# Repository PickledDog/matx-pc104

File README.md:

# matx-pc104
 microATX carrier board for PC/104 SBCs

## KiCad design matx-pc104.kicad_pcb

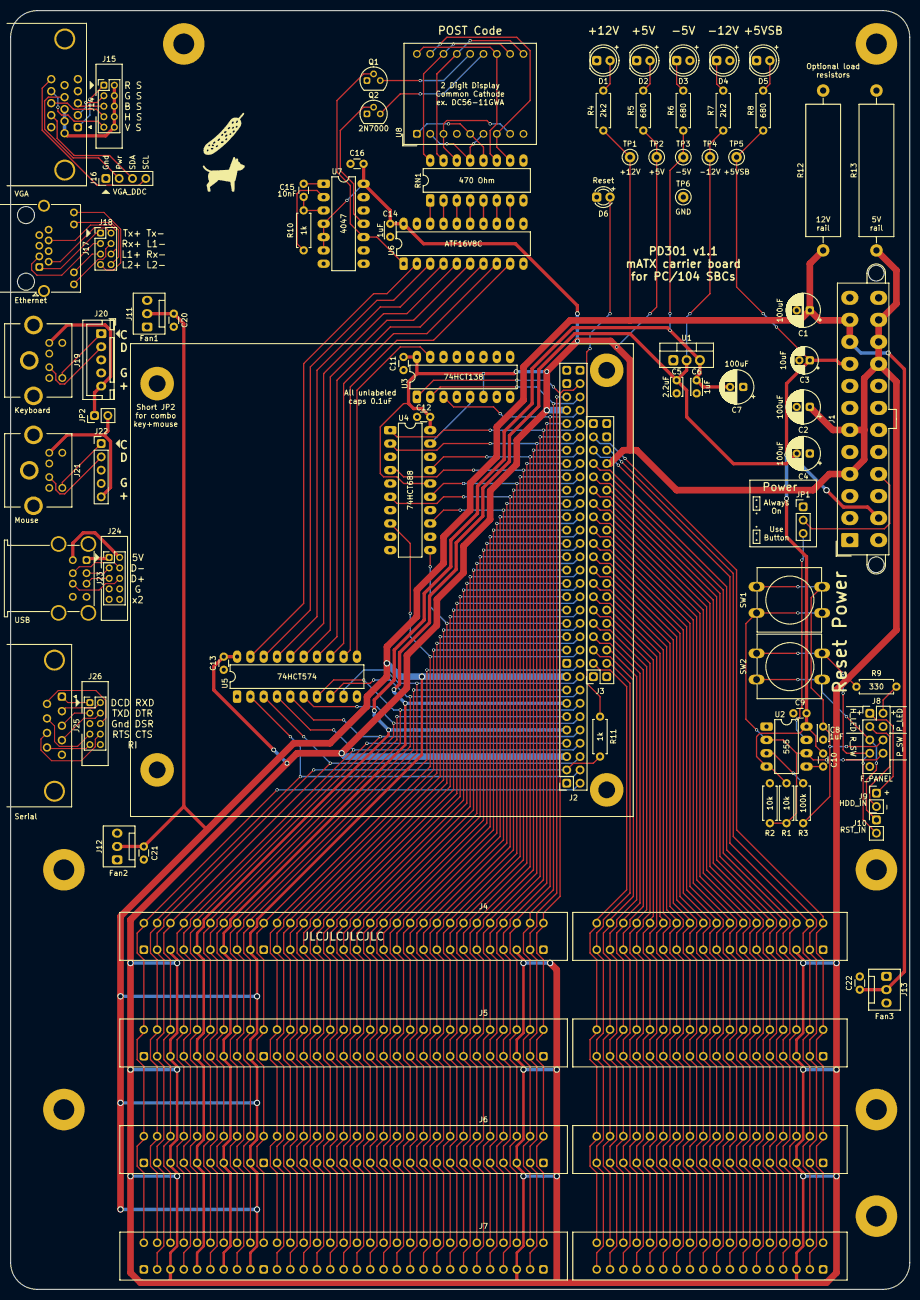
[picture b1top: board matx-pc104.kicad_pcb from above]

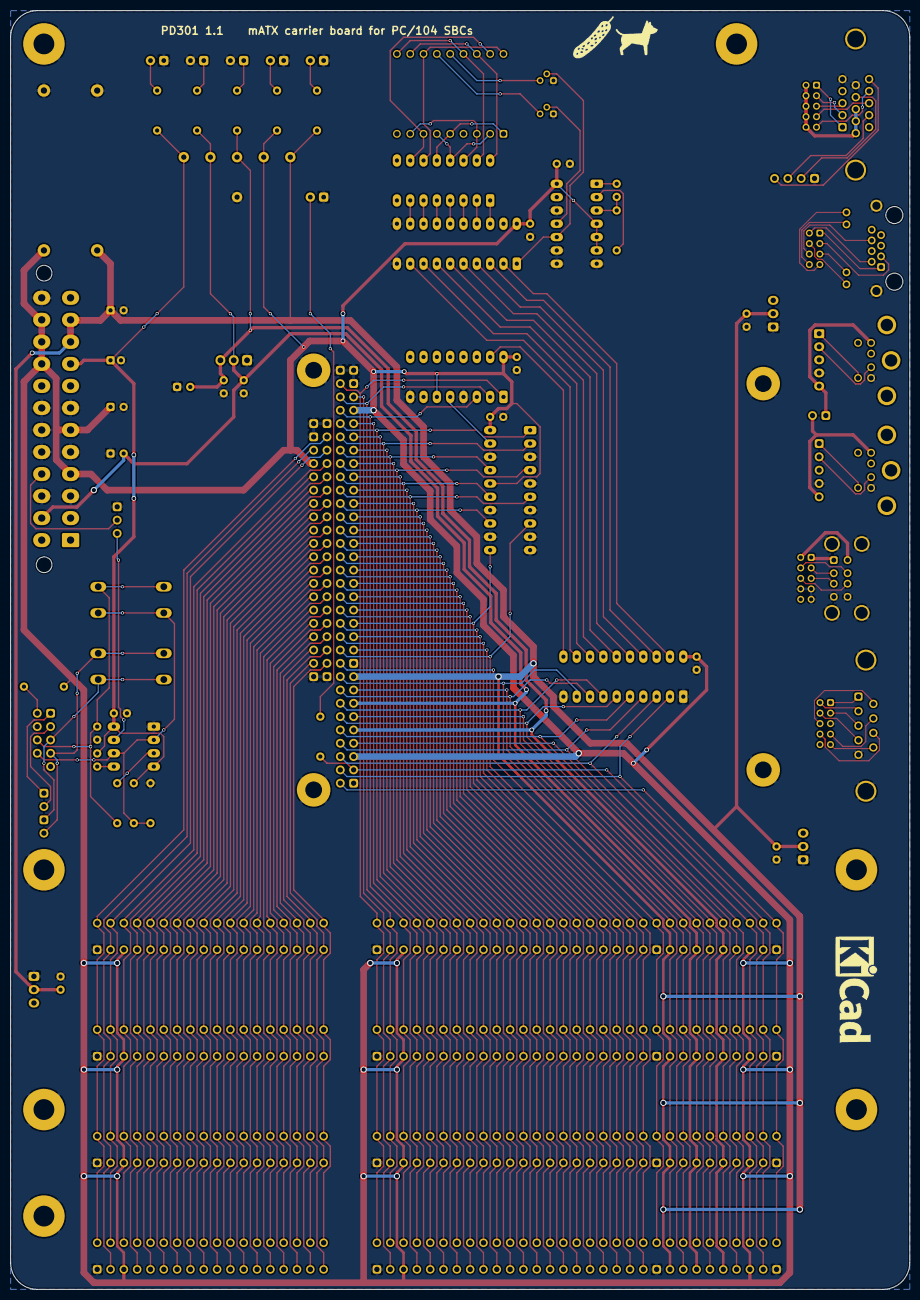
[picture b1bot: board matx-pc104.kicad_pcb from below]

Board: 2 copper layers, 171.4 x 243.8 mm, 100 parts (2 on the bottom side), 180 nets.

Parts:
C1, C2, C4, C7: 100uF; CP_Radial_D6.3mm_P2.50mm
C3: 10uF; CP_Radial_D5.0mm_P2.00mm
C5: 2.2uF; C_Disc_D3.4mm_W2.1mm_P2.50mm
C6, C8, C14: 1uF; C_Disc_D3.0mm_W2.0mm_P2.50mm
C9, C10, C11, C12, C13, C16, C20, C21, C22: 0.1uF; C_Disc_D3.0mm_W1.6mm_P2.50mm
C15: 10nF; C_Disc_D3.0mm_W1.6mm_P2.50mm
D1: +12V; LED_D5.0mm
D2: +5V; LED_D5.0mm
D3: -5V; LED_D5.0mm
D4: -12V; LED_D5.0mm
D5: +5VSB; LED_D5.0mm
D6: Reset; LED_D3.0mm
H1, H2, H3, H4, H5, H6, H7: MountHole; MountingHole_156mil_Pad
H8, H9, H10, H11: MountHole; MountingHole_3.2mm_M3_Pad
J1: ATX-24; Molex_Mini-Fit_Jr_5566-24A2_2x12_P4.20mm_Vertical
J2: PC104-8; PinSocket_2x32_P2.54mm_Vertical
J3: PC104-16; PinSocket_2x20_P2.54mm_Vertical
J4, J5, J6, J7: Bus_ISA_16bit; BUS_AT_Socket
J8: F_PANEL; PinHeader_2x05_P2.54mm_Vertical_Delete10
J9: HDD_IN; PinHeader_1x02_P2.54mm_Vertical
J10: RST_IN; PinHeader_1x02_P2.54mm_Vertical
J11: Fan1; FanPinHeader_1x03_P2.54mm_Vertical
J12: Fan2; FanPinHeader_1x03_P2.54mm_Vertical
J13: Fan3; FanPinHeader_1x03_P2.54mm_Vertical
J14: VGA; DSUB-15-HD_Female_Horizontal_P2.29x2.54mm_Housed
J15: VGA; PinHeader_2x05_P2.00mm_Vertical
J16: VGA_DDC; PinHeader_1x04_P2.54mm_Vertical
J17: Ethernet; RJ45_Amphenol_RJHSE538X
J18: Ethernet; PinHeader_2x04_P2.00mm_Vertical
J19: Keyboard; Mini-DIN-6-Socket
J20: Keyboard; JST_XH_B5B-XH-A_1x05_P2.50mm_Vertical
J21: Mouse; Mini-DIN-6-Socket
J22: Mouse; PinHeader_1x05_P2.54mm_Vertical
J23: USB; USB_A_Wuerth_61400826021_Horizontal_Stacked
J24: USB; PinHeader_2x05_P2.00mm_Vertical
J25: Serial; DSUB-9_Male_Horizontal_P2.77x2.84mm_EdgePinOffset7.70mm_Hou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
J26: Serial; PinHeader_2x05_P2.00mm_Vertical
JP1: ForceOn; PinHeader_1x03_P2.54mm_Vertical
JP2: K_5V=M_5V; PinHeader_1x02_P2.54mm_Vertical
Q1, Q2: 2N7000; TO-92
R1, R2: 10k; R_Axial_DIN0207_L6.3mm_D2.5mm_P7.62mm_Horizontal
R3: 100k; R_Axial_DIN0207_L6.3mm_D2.5mm_P7.62mm_Horizontal
R4, R7: 2k2; R_Axial_DIN0207_L6.3mm_D2.5mm_P7.62mm_Horizontal
R5, R6, R8: 680; R_Axial_DIN0207_L6.3mm_D2.5mm_P7.62mm_Horizontal
R9: 330; R_Axial_DIN0207_L6.3mm_D2.5mm_P7.62mm_Horizontal
R10, R11: 1k; R_Axial_DIN0207_L6.3mm_D2.5mm_P7.62mm_Horizontal
R12: 20; R_Axial_Power_L25.0mm_W6.4mm_P30.48mm
R13: 4.7; R_Axial_Power_L25.0mm_W6.4mm_P30.48mm
RN1: 470 Ohm; DIP-16_W7.62mm_LongPads
Ref**: Val**; Symbol-Dog-8mm
Ref**#2, Ref**#4: Val**; Symbol-Pickle-8mm
Ref**#3: Val**; Symbol-Dog-8mm
SW1: Power; SW_PUSH-12mm
SW2: Reset; SW_PUSH-12mm
TP1: +12V; TestPoint_Loop_D1.80mm_Drill1.0mm_Beaded
TP2: +5V; TestPoint_Loop_D1.80mm_Drill1.0mm_Beaded
TP3: -5V; TestPoint_Loop_D1.80mm_Drill1.0mm_Beaded
TP4: -12V; TestPoint_Loop_D1.80mm_Drill1.0mm_Beaded
TP5: +5VSB; TestPoint_Loop_D1.80mm_Drill1.0mm_Beaded
TP6: GND; TestPoint_Loop_D1.80mm_Drill1.0mm_Beaded
U1: L7905; TO-220-3_Vertical
U2: 555; DIP-8_W7.62mm_LongPads
U3: 74HCT138; DIP-16_W7.62mm_LongPads
U4: 74HCT688; DIP-20_W7.62mm_LongPads
U5: 74HCT574; DIP-20_W7.62mm_LongPads
U6: ATF16V8C; DIP-20_W7.62mm_LongPads
U7: 4047; DIP-14_W7.62mm_LongPads
U8: DC56-11GWA; DA56-11CGKWA

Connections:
+5V: C2.1, C11.2, C12.2, C13.2, C14.2, C16.2, J1.4, J1.6, J1.21, J1.22, J1.23, J2.5, J2.57, J3.34, J4.3, J4.29, J4.78, J5.3, J5.29, J5.78, J6.3, J6.29, J6.78, J7.3, J7.29, J7.78, R5.1, R9.1, R13.1, TP2.1, U3.6, U3.16, U4.16, U4.20, U5.20, U6.20, U7.4, U7.5, U7.6, U7.14
+5VSB: C3.1, C9.2, C10.1, J1.9, R1.2, R8.1, TP5.1, U2.4, U2.8
+12V: C1.1, C20.1, C21.1, C22.1, J1.10, J1.11, J2.17, J4.9, J5.9, J6.9, J7.9, J11.2, J12.2, J13.2, R4.1, R12.1, TP1.1
-5V: C6.2, C7.2, J2.9, J4.5, J5.5, J6.5, J7.5, R6.1, TP3.1, U1.3
-12V: C4.2, C5.2, J1.14, J2.13, J4.7, J5.7, J6.7, J7.7, R7.1, TP4.1, U1.2
/A0: J2.62, J4.62, J5.62, J6.62, J7.62, U3.1
/A1: J2.60, J4.61, J5.61, J6.61, J7.61, U3.2
/A2: J2.58, J4.60, J5.60, J6.60, J7.60, U3.3
/A3: J2.56, J4.59, J5.59, J6.59, J7.59, U4.1
/A4: J2.54, J4.58, J5.58, J6.58, J7.58, U4.2
/A5: J2.52, J4.57, J5.57, J6.57, J7.57, U4.17
/A6: J2.50, J4.56, J5.56, J6.56, J7.56, U4.4
/A7: J2.48, J4.55, J5.55, J6.55, J7.55, U4.15
/A8: J2.46, J4.54, J5.54, J6.54, J7.54, U4.6
/A9: J2.44, J4.53, J5.53, J6.53, J7.53, U4.13
/A10: J2.42, J4.52, J5.52, J6.52, J7.52
/A11: J2.40, J4.51, J5.51, J6.51, J7.51
/A12: J2.38, J4.50, J5.50, J6.50, J7.50
/A13: J2.36, J4.49, J5.49, J6.49, J7.49
/A14: J2.34, J4.48, J5.48, J6.48, J7.48
/A15: J2.32, J4.47, J5.47, J6.47, J7.47
/A16: J2.30, J4.46, J5.46, J6.46, J7.46
/A17: J2.28, J4.45, J5.45, J6.45, J7.45
/A18: J2.26, J4.44, J5.44, J6.44, J7.44
/A19: J2.24, J4.43, J5.43, J6.43, J7.43
/AEN: J2.22, J4.42, J5.42, J6.42, J7.42, U4.8
/ALE: J2.55, J4.28, J5.28, J6.28, J7.28
/CLK: J2.39, J4.20, J5.20, J6.20, J7.20
/CV: C10.2, U2.5
/D0: J2.18, J4.40, J5.40, J6.40, J7.40, U5.9
/D1: J2.16, J4.39, J5.39, J6.39, J7.39, U5.8
/D2: J2.14, J4.38, J5.38, J6.38, J7.38, U5.7
/D3: J2.12, J4.37, J5.37, J6.37, J7.37, U5.6
/D4: J2.10, J4.36, J5.36, J6.36, J7.36, U5.5
/D5: J2.8, J4.35, J5.35, J6.35, J7.35, U5.4
/D6: J2.6, J4.34, J5.34, J6.34, J7.34, U5.3
/D7: J2.4, J4.33, J5.33, J6.33, J7.33, U5.2
/D8: J3.23, J4.91, J5.91, J6.91, J7.91
/D9: J3.25, J4.92, J5.92, J6.92, J7.92
/D10: J3.27, J4.93, J5.93, J6.93, J7.93
/D11: J3.29, J4.94, J5.94, J6.94, J7.94
/D12: J3.31, J4.95, J5.95, J6.95, J7.95
/D13: J3.33, J4.96, J5.96, J6.96, J7.96
/D14: J3.35, J4.97, J5.97, J6.97, J7.97
/D15: J3.37, J4.98, J5.98, J6.98, J7.98
/DIC1_CC: Q1.3, U8.14
/DIG2_CC: Q2.3, U8.13
/DIG_A: RN1.1, U6.18
/DIG_A': RN1.16, U8.11, U8.16
/DIG_B: RN1.2, U6.17
/DIG_B': RN1.15, U8.10, U8.15
/DIG_C: RN1.3, U6.16
/DIG_C': RN1.14, U8.3, U8.8
/DIG_D: RN1.4, U6.15
/DIG_D': RN1.13, U8.2, U8.6
/DIG_E: RN1.5, U6.14
/DIG_E': RN1.12, U8.1, U8.5
/DIG_F: RN1.6, U6.13
/DIG_F': RN1.11, U8.12, U8.18
/DIG_G: RN1.7, U6.12
/DIG_G': RN1.10, U8.7, U8.17
/DRQ0: J3.20, J4.71, J5.71, J6.71, J7.71
/DRQ1: J2.35, J4.18, J5.18, J6.18, J7.18
/DRQ2: J2.11, J4.6, J5.6, J6.6, J7.6
/DRQ3: J2.31, J4.16, J5.16, J6.16, J7.16
/DRQ5: J3.24, J4.73, J5.73, J6.73, J7.73
/DRQ6: J3.28, J4.75, J5.75, J6.75, J7.75
/DRQ7: J3.32, J4.77, J5.77, J6.77, J7.77
/E_L1+: J17.10, J18.5
/E_L1-: J17.9, J18.4
/E_L2+: J17.12, J18.7
/E_L2-: J17.11, J18.8
/E_RX+: J17.3, J18.3
/E_RX-: J17.6, J18.6
/E_TX+: J17.1, J18.1
/E_TX-: J17.2, J18.2
/FB: R3.2, U2.3
/HDD_A: J8.1, J9.1
/HDD_B: J8.3, J9.2
/IORDY: J2.20, J4.41, J5.41, J6.41, J7.41
/IRQ2: J2.7, J4.4, J5.4, J6.4, J7.4
/IRQ3: J2.49, J4.25, J5.25, J6.25, J7.25
/IRQ4: J2.47, J4.24, J5.24, J6.24, J7.24
/IRQ5: J2.45, J4.23, J5.23, J6.23, J7.23
/IRQ6: J2.43, J4.22, J5.22, J6.22, J7.22
/IRQ7: J2.41, J4.21, J5.21, J6.21, J7.21
/IRQ10: J3.8, J4.65, J5.65, J6.65, J7.65
/IRQ11: J3.10, J4.66, J5.66, J6.66, J7.66
/IRQ12: J3.12, J4.67, J5.67, J6.67, J7.67
/IRQ14: J3.16, J4.69, J5.69, J6.69, J7.69
/IRQ15: J3.14, J4.68, J5.68, J6.68, J7.68
/K_5V: J19.4, J20.5, JP2.1
/K_CLK: J19.5, J20.1
/K_DAT: J19.1, J20.2
/L+5: D2.2, R5.2
/L+5S: D5.2, R8.2
/L+12: D1.2, R4.2
/L-5: D3.1, R6.2
/L-12: D4.1, R7.2
/LA17: J3.17, J4.88, J5.88, J6.88, J7.88
/LA18: J3.15, J4.87, J5.87, J6.87, J7.87
/LA19: J3.13, J4.86, J5.86, J6.86, J7.86
/LA20: J3.11, J4.85, J5.85, J6.85, J7.85
/LA21: J3.9, J4.84, J5.84, J6.84, J7.84
/LA22: J3.7, J4.83, J5.83, J6.83, J7.83
/LA23: J3.5, J4.82, J5.82, J6.82, J7.82
/LCLK: Q1.2, U6.1, U7.10
/L_R: D6.2, R11.1
/M_5V: J21.4, J22.5, JP2.2
/M_CLK: J21.5, J22.1
/M_DAT: J21.1, J22.2
/OSC: J2.59, J4.30, J5.30, J6.30, J7.30
/O_C: C15.2, U7.1
/O_R: R10.2, U7.2
/O_RC: C15.1, R10.1, U7.3
/PC0: U5.12, U6.9
/PC1: U5.13, U6.8
/PC2: U5.14, U6.7
/PC3: U5.15, U6.6
/PC4: U5.16, U6.5
/PC5: U5.17, U6.4
/PC6: U5.18, U6.3
/PC7: U5.19, U6.2
/PWR_A: C8.1, J8.6, R3.1, SW1.1
/PWR_B: J8.8, R1.1, R2.1, SW1.2, U2.2, U2.6
/PWR_LED: J8.2, R9.2
/RESET: J2.3, J4.2, J5.2, J6.2, J7.2, R11.2
/RST_A: J8.5, J10.1, SW2.2
/RST_B: J8.7, J10.2, SW2.1
/SHBE: J3.3, J4.81, J5.81, J6.81, J7.81
/S_CTS: J25.8, J26.8
/S_DCD: J25.1, J26.1
/S_DSR: J25.6, J26.6
/S_DTR: J25.4, J26.4
/S_RI: J25.9, J26.9
/S_RTS: J25.7, J26.7
/S_RX: J25.2, J26.2
/S_TX: J25.3, J26.3
/TC: J2.53, J4.27, J5.27, J6.27, J7.27
/U1_5V: J23.1, J24.1
/U1_D+: J23.3, J24.5
/U1_D-: J23.2, J24.3
/U2_5V: J23.5, J24.2
/U2_D+: J23.7, J24.6
/U2_D-: J23.6, J24.4
/V_B: J14.3, J15.5
/V_G: J14.2, J15.3
/V_GND: J14.6, J14.7, J14.8, J15.2, J15.4, J15.6, J15.8, J15.10
/V_HS: J14.13, J15.7
/V_PWR: J14.9, J16.2
/V_R: J14.1, J15.1
/V_SCL: J14.15, J16.4
/V_SDA: J14.12, J16.3
/V_VS: J14.14, J15.9
/~DACK0: J3.18, J4.70, J5.70, J6.70, J7.70
/~DACK1: J2.33, J4.17, J5.17, J6.17, J7.17
/~DACK2: J2.51, J4.26, J5.26, J6.26, J7.26
/~DACK3: J2.29, J4.15, J5.15, J6.15, J7.15
/~DACK5: J3.22, J4.72, J5.72, J6.72, J7.72
/~DACK6: J3.26, J4.74, J5.74, J6.74, J7.74
/~DACK7: J3.30, J4.76, J5.76, J6.76, J7.76
/~IOCHK: J2.2, J4.32, J5.32, J6.32, J7.32
/~IOCS16: J3.6, J4.64, J5.64, J6.64, J7.64
/~IOR: J2.27, J4.14, J5.14, J6.14, J7.14
/~IOW: J2.25, J4.13, J5.13, J6.13, J7.13, U4.11
/~IOW8x: U3.5, U4.19
/~LCLK: Q2.2, U7.11
/~MASTER: J3.36, J4.79, J5.79, J6.79, J7.79
/~MEMCS16: J3.4, J4.63, J5.63, J6.63, J7.63
/~MEMR: J3.19, J4.89, J5.89, J6.89, J7.89
/~MEMW: J3.21, J4.90, J5.90, J6.90, J7.90
/~NOWS: J2.15, J4.8, J5.8, J6.8, J7.8
/~POST_CS: U3.15, U5.11
/~PS_ON: J1.16, JP1.2
/~PWR_CTRL: JP1.3, U2.7
/~REFRESH: J2.37, J4.19, J5.19, J6.19, J7.19
/~SMEMR: J2.23, J4.12, J5.12, J6.12, J7.12
/~SMEMW: J2.21, J4.11, J5.11, J6.11, J7.11
GND: C1.2, C2.2, C3.2, C4.1, C5.1, C6.1, C7.1, C8.2, C9.1, C11.1, C12.1, C13.1, C14.1, C16.1, C20.2, C21.2, C22.2, D1.1, D2.1, D3.2, D4.2, D5.1, D6.1, H1.1, H2.1, H3.1, H4.1, H5.1, H6.1, H7.1, H8.1, H9.1, H10.1, H11.1, J1.3, J1.5, J1.7, J1.15, J1.17, J1.18, J1.19, J1.24, J2.1, J2.19, J2.61, J2.63, J2.64, J3.1, J3.2, J3.38, J3.39, J3.40, J4.1, J4.10, J4.31, J4.80, J5.1, J5.10, J5.31, J5.80, J6.1, J6.10, J6.31, J6.80, J7.1, J7.10, J7.31, J7.80, J8.4, J11.1, J12.1, J13.1, J14.0, J14.5, J14.10, J16.1, J17.SH, J19.3, J20.4, J21.3, J22.4, J23.4, J23.8, J23.9, J24.7, J24.8, J24.9, J25.0, J25.5, J26.5, JP1.1, Q1.1, Q2.1, R2.2, R12.2, R13.2, TP6.1, U1.1, U2.1, U3.4, U3.8, U4.3, U4.5, U4.7, U4.9, U4.10, U4.12, U4.14, U4.18, U5.1, U5.10, U6.10, U6.11, U7.7, U7.8, U7.9, U7.12
unnamed: J1.1, J1.2, J1.12, J1.13

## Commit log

2021-09-09 Initial commit of PD301 / matx-pc104
2021-09-11 Correct silkscreen - fix VGA pinout, align port labels
2021-09-20 Version 1.1. Fix reset issue
    Replace reset circuit with passthrough, increase LED decoder cap value, enlarge load resistor footprints, renumber some components
2021-09-20 Add code for the ATF16V8C
2021-10-10 Add silk to aid orientation of backpanel connections
2021-10-14 Add design for ATX I/O shield
2021-12-02 Adjust backpanel design for better fit
    Move Ethernet jack to be flush through backpanel, make per-port cutouts for USB
2022-07-11 Add jumper to link keyboard & mouse power
